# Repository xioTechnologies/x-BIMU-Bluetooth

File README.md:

x-BIMU-Bluetooth
================

XBee form factor breakout for the Microchip [RN41](http://www.microchip.com/wwwproducts/Devices.aspx?product=RN41) or [RN42](http://www.microchip.com/wwwproducts/Devices.aspx?product=RN42).  The design is identical to the [RN42-XV](http://www.microchip.com/wwwproducts/Devices.aspx?product=RN42XV) with the exception that pin 9 can be used to power down the device via a FET (equivalent to the sleep pin on XBee modules).

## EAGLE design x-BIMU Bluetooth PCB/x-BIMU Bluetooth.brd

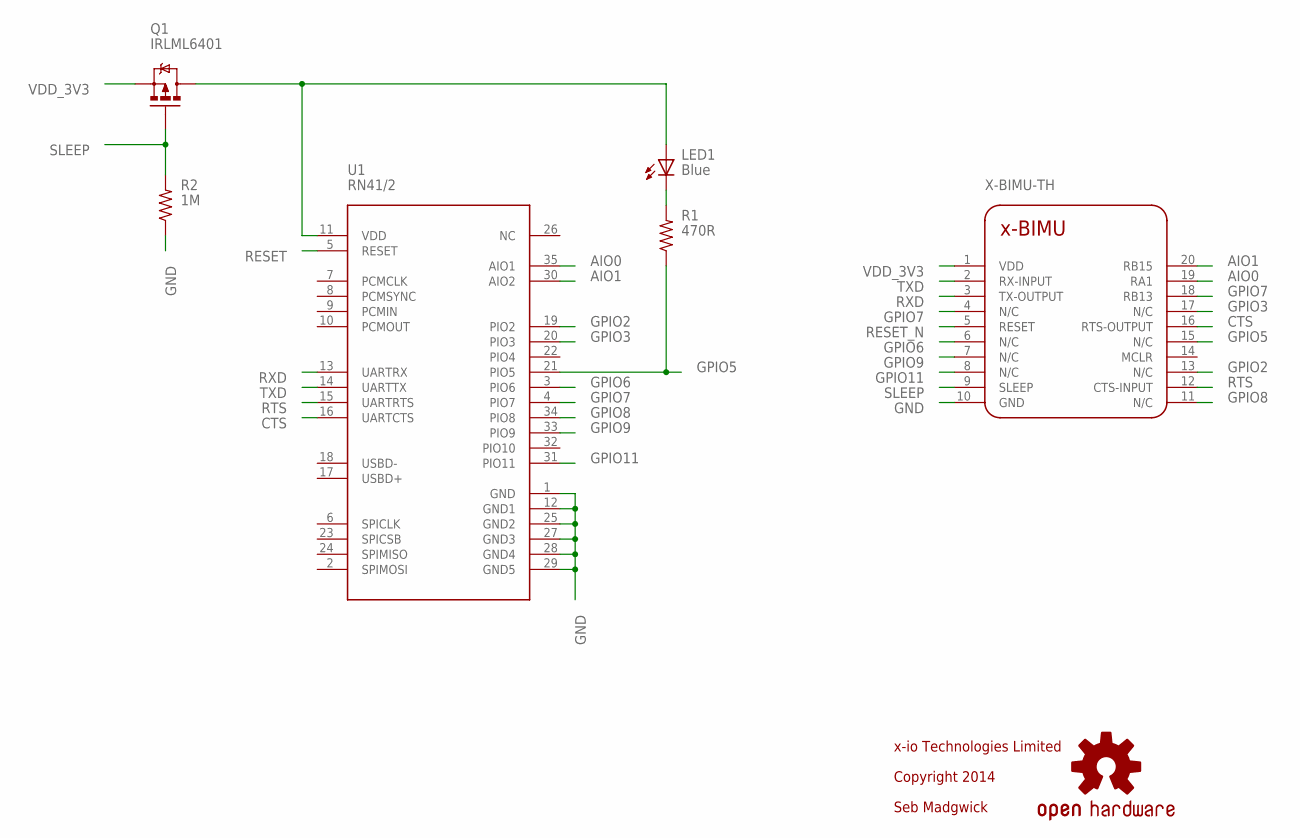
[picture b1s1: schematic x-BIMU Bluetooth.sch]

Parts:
LED1: Blue; LED-0603
Q1: IRLML6401; SOT23
R1: 470R; 0402-RES
R2: 1M; 0402-RES
U1: RN41/2; RN41
U2: X-BIMU-TH; X-BIMU_TH
U$3: OSHW-LOGOS; OSHW-LOGO-S

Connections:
AIO0: U1.35 (AIO1), U2.19 (RA1)
AIO1: U1.30 (AIO2), U2.20 (RB15)
CTS: U1.16 (UARTCTS), U2.16 (RTS-OUTPUT)
GND: R2.1, U1.1 (GND), U1.12 (GND1), U1.25 (GND2), U1.27 (GND3), U1.28 (GND4), U1.29 (GND5), U2.10 (GND)
GPIO2: U1.19 (PIO2), U2.13 (N/C)
GPIO3: U1.20 (PIO3), U2.17 (N/C)
GPIO5: R1.1, U1.21 (PIO5), U2.15 (N/C)
GPIO6: U1.3 (PIO6), U2.6 (N/C)
GPIO7: U1.4 (PIO7), U2.4 (N/C), U2.18 (RB13)
GPIO8: U1.34 (PIO8), U2.11 (N/C)
GPIO9: U1.33 (PIO9), U2.7 (N/C)
GPIO11: U1.31 (PIO11), U2.8 (N/C)
unnamed: LED1.A, Q1.3 (D), U1.11 (VDD)
unnamed: LED1.C, R1.2
RESET: U1.5 (RESET)
RESET_N: U2.5 (RESET)
RTS: U1.15 (UARTRTS), U2.12 (CTS-INPUT)
RXD: U1.13 (UARTRX), U2.3 (TX-OUTPUT)
SLEEP: Q1.1 (G), R2.2, U2.9 (SLEEP)
TXD: U1.14 (UARTTX), U2.2 (RX-INPUT)
VDD_3V3: Q1.2 (S), U2.1 (VDD)

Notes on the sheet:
Seb Madgwick
Copyright 2014
x-io Technologies Limited

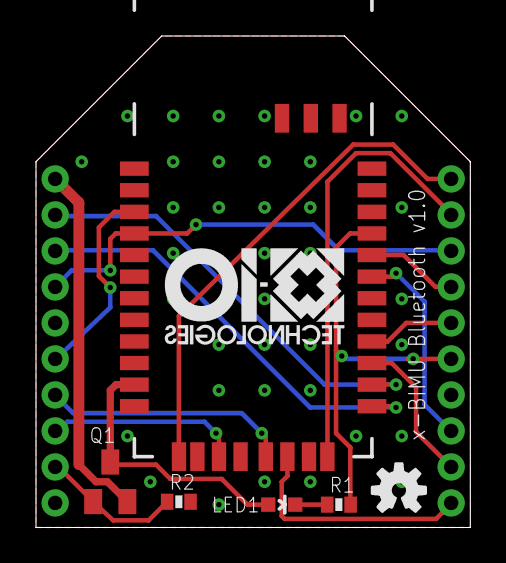
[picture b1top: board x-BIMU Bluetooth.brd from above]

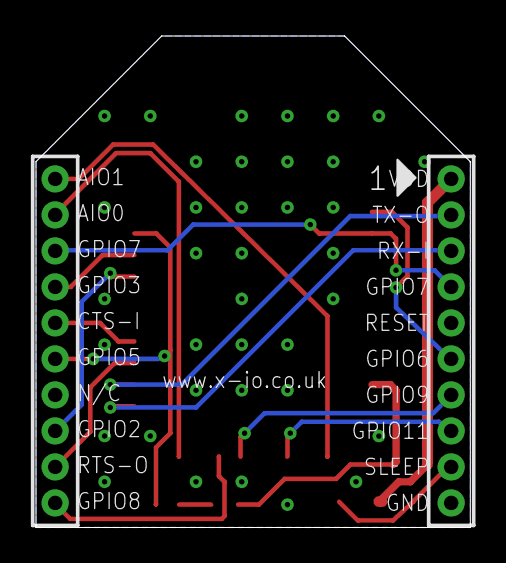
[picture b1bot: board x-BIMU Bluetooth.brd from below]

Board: 2 copper layers, 24.1 x 27.3 mm, 10 parts (2 on the bottom side), 19 nets.

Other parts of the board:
U$1: X-IO_TECHNOLOGIES_LOGO_10MM_BOTTOM
U$2: X-BIMU_BLUETOOTH_V1_0_BOTTOM
U$4: X-BIMU_BLUETOOTH_V1_0_TOP

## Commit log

2014-04-08 Add project files
2014-04-24 Add photo

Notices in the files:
parts and their libraries:
SparkFun: Licensing: CC v3.0 Share-Alike You are welcome to use this library for commercial purposes.
